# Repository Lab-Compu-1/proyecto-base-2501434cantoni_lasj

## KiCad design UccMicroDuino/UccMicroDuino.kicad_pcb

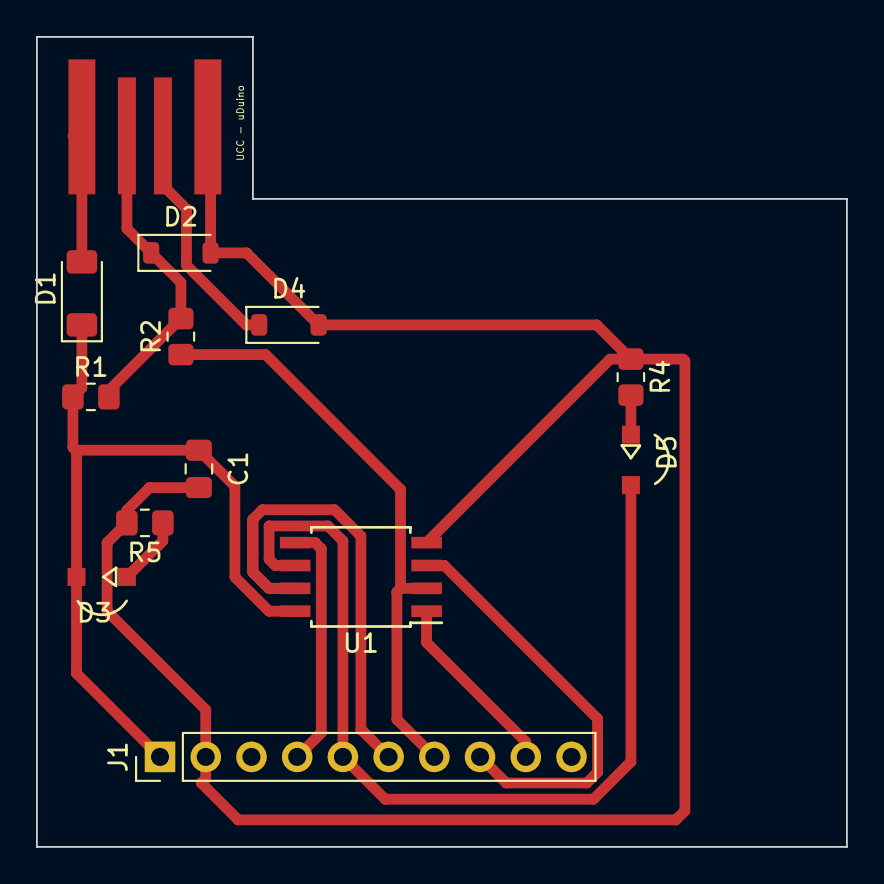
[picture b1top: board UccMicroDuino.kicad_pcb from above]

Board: 2 copper layers, 45.0 x 45.0 mm, 13 parts (0 on the bottom side), 13 nets.

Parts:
C1: 0.1 u; C_0805_2012Metric_Pad1.18x1.45mm_HandSolder
D1: PMLL4148L; D_MiniMELF
D2, D4: 3.6V 1/2mW; D_SOD-123
D3: Led Red; ledSMD
D5: LED Green; ledSMD
J1: Header; PinHeader_1x10_P2.54mm_Vertical
J2: Pcb USB Type A; USB_A_UCC
R1: 1.5 Ohms 5% 1/8w; R_0805_2012Metric_Pad1.20x1.40mm_HandSolder
R2: 68 Ohms 5% 1/8W; R_0805_2012Metric_Pad1.20x1.40mm_HandSolder
R4, R5: 330 Ohms 5% 1/8W; R_0805_2012Metric_Pad1.20x1.40mm_HandSolder
U1: ATtiny85-20S; SOIC-8W_5.3x5.3mm_P1.27mm

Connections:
+5V: C1.1, D1.1 (K), D3.2 (A), J1.1, R1.1, U1.8 (VCC)
GND: C1.2, D2.2 (A), D4.2 (A), J1.2, J2.4 (GND), R4.1, R5.2, U1.4 (GND)
unnamed: D1.2 (A), J2.1 (VBUS)
unnamed: D2.1 (K), J2.2 (D-), R1.2, R2.2
unnamed: D3.1 (K), R5.1
unnamed: D4.1 (K), J2.3 (D+)
unnamed: D5.2 (A), J1.5, U1.6 (PB1)
unnamed: D5.1 (K), R4.2
unnamed: J1.4, U1.5 (AREF/PB0)
unnamed: J1.6, U1.7 (PB2)
unnamed: J1.7, R2.1, U1.2 (XTAL1/PB3)
unnamed: J1.8, U1.3 (XTAL2/PB4)
unnamed: J1.9, U1.1 (~RESET/PB5)

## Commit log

2025-03-17 GitHub Classroom Feedback
2025-03-17 Setting up GitHub Classroom Feedback
2025-04-07 Plano eléctrico 1
2025-05-14 Placa y rutas
2025-05-19 Commit para subir
